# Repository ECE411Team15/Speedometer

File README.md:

# Speedometer
ECE 411, Fall 2017, Speedometer project.

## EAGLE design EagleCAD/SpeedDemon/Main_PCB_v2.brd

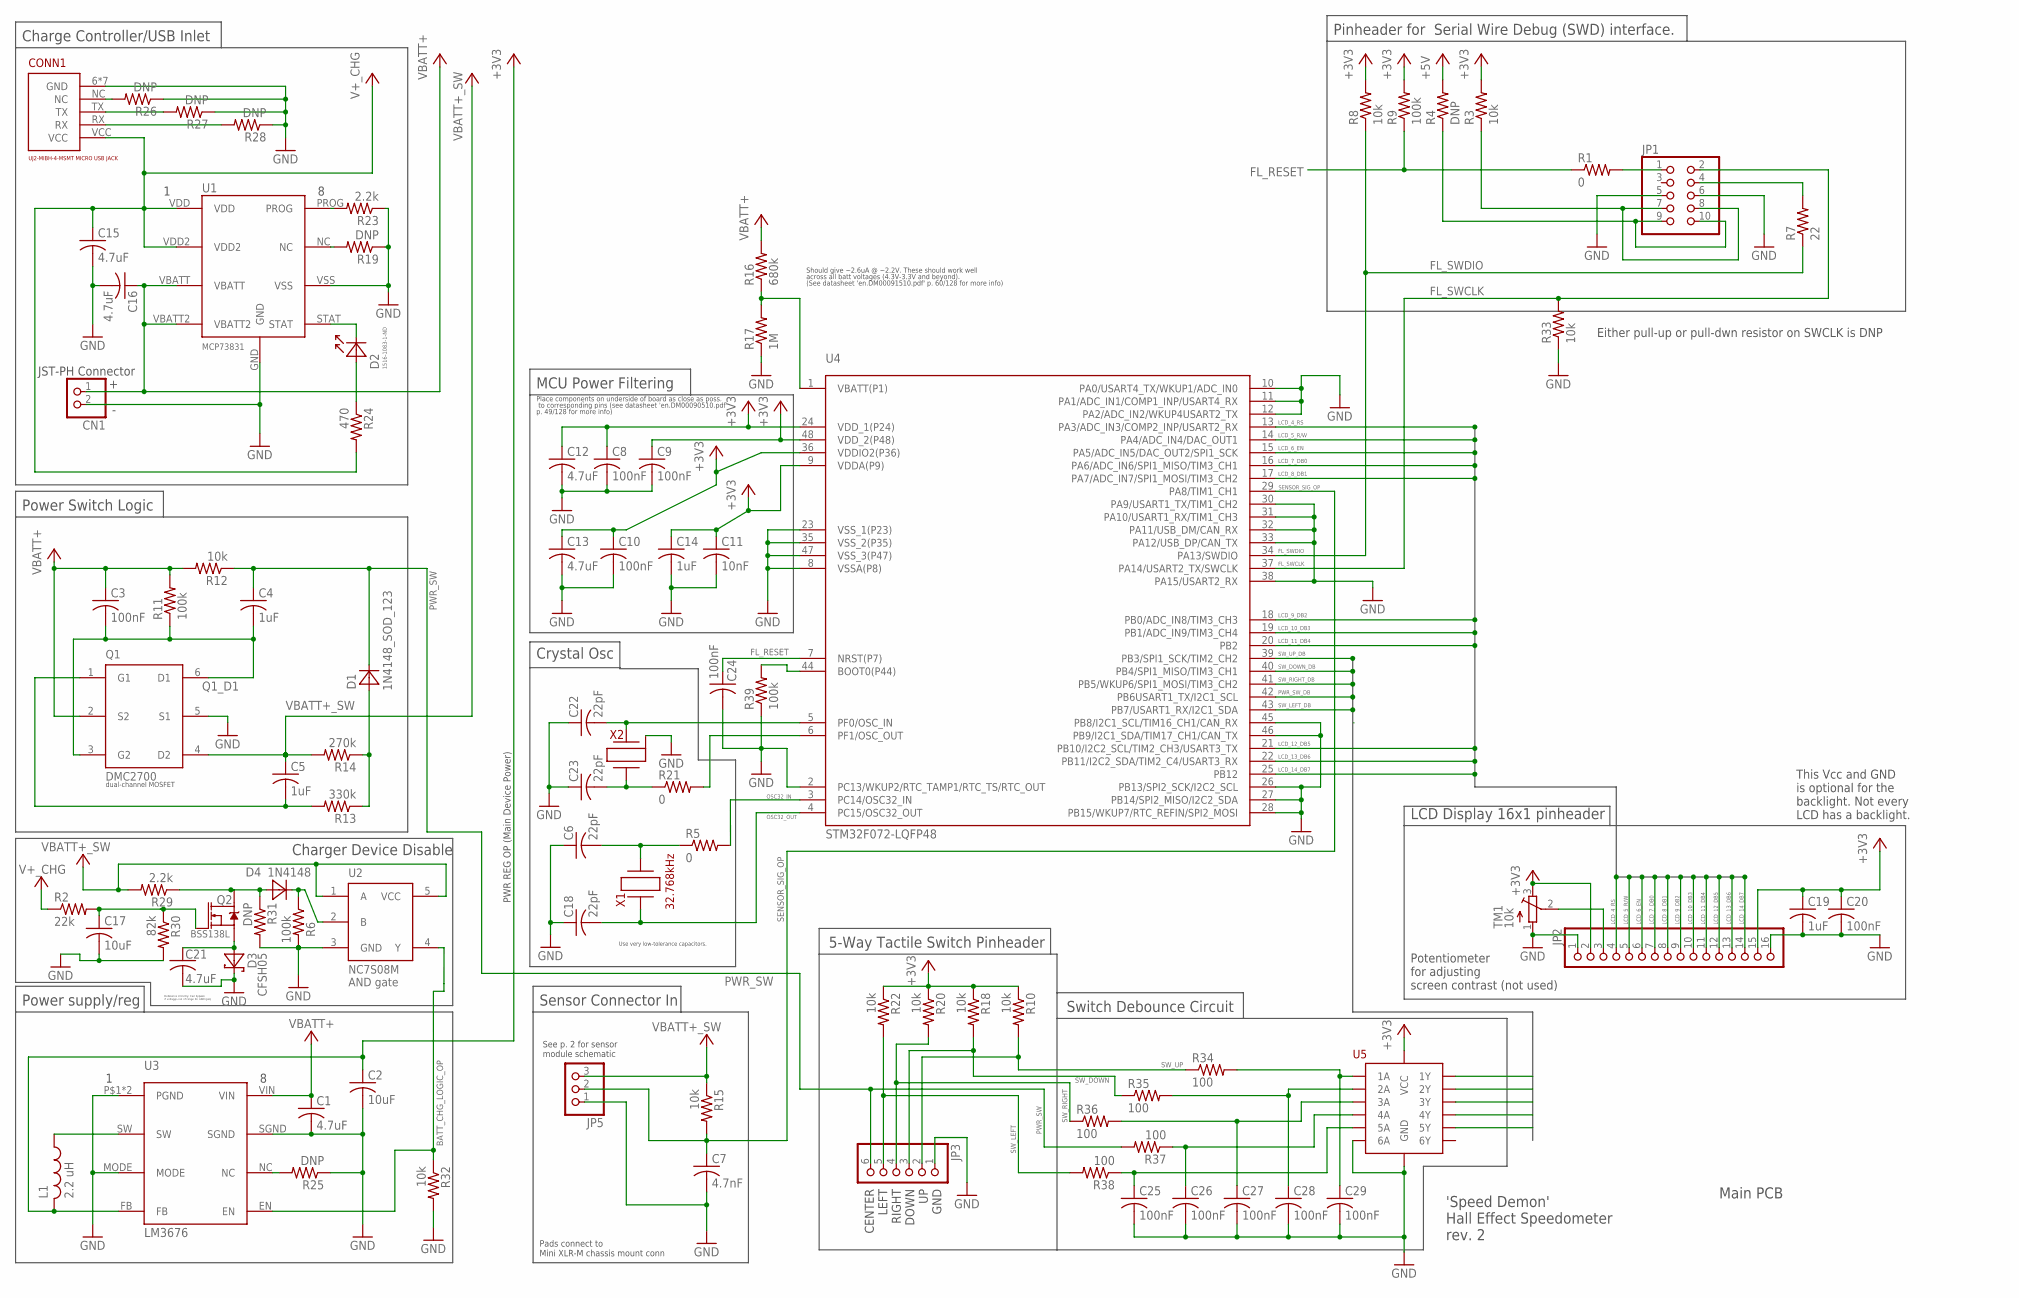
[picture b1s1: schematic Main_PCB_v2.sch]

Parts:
C1, C12, C13, C15, C16, C21: 4.7uF; C_0805
C2, C17: 10uF; C_0805
C3, C8, C9, C10, C20, C24, C25, C26, C27, C28, C29: 100nF; C_0805
C4, C5, C14, C19: 1uF; C_0805
C6, C18, C22, C23: 22pF; C_0805
C7: 4.7nF; C_0805
C11: 10nF; C_0805
CN1: JST_2PIN-SMT-RA; JST-PH-2-SMT-RA
CONN1: USB_JACK_102-4008-1-ND_USB-MICRO-B; USB_JACK_102-4008-1-ND_UJ2-MIBH-4-MSMT-TR
D1: 1N4148_SOD_123; D_SOD_123
D2: LED_0805
D3: CFSH05; SOD-882
D4: 1N4148; D_SOD_123
JP1: PINHD-2X5; 2X05
JP2: PINHD-1X16; 1X16
JP3: PINHD-1X6; 1X06
JP5: PINHD-1X3; 1X03
L1: 2.2 uH; NONSTANDARD_IND
Q1: DMC2700; SOT-23-6
Q2: BSS138L; TO-236
R1, R5: 0; R0805
R2: 22k; R_0805
R3, R8, R33: 10k; R0805
R4: DNP; R0805
R6, R11, R39: 100k; R_0805
R7: 22; R0805
R9: 100k; R0805
R10, R12, R15, R18, R20, R22, R32: 10k; R_0805
R13: 330k; R_0805
R14: 270k; R_0805
R16: 680k; R_0805
R17: 1M; R_0805
R19, R25, R26, R27, R28, R31: DNP; R_0805
R21: 0; R_0805
R23, R29: 2.2k; R_0805
R24: 470; R_0805
R30: 82k; R_0805
R34, R35, R36, R37, R38: 100; R_0805
TM1: 10k; TRIM-3386
U1: MCP73831_8-DFN; 8-DFN-(2X3)
U2: NC7S08M; SOT-23-5
U3: LM3676; WSON
U4: STM32F072-LQFP48; LQFP48
U5: SN74LV14A_HEX_SHMITT; S-PVFQN-N14
X1: 32.768kHz; CRYSTAL_OSC_3.2X1.5
X2: ABM3B-8.000MHZ-10-D-1-G-T; 4-SMD

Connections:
+3V3: C2.1, C8.1, C9.1, C10.1, C11.1, C12.1, C13.1, C14.1, C19.1, C20.1, JP2.2, JP2.15, L1.P$2 (2), R3.2, R8.2, R9.2, R10.1, R18.1, R20.1, R22.1, TM1.3 (E), U3.FB, U4.9 (VDDA(P9)), U4.24 (VDD_1(P24)), U4.36 (VDDIO2(P36)), U4.48 (VDD_2(P48)), U5.P$14 (VCC)
+5V: R4.2
+V+_CHG: C15.1, CONN1.VCC, R2.1, R24.2, U1.VDD, U1.VDD2
BATT_CHG_LOGIC_OP: R32.1, U2.4 (Y), U3.EN
FL_RESET: C24.1, R1.1, R9.1, U4.7 (NRST(P7))
FL_SWCLK: JP1.2, R33.2, U4.37 (PA14/USART2_TX/SWCLK)
FL_SWDIO: R7.1, R8.1, U4.34 (PA13/SWDIO)
GND: C1.2, C2.2, C6.1, C7.2, C8.2, C9.2, C10.2, C11.2, C12.2, C13.2, C14.2, C15.2, C16.2, C17.2, C18.1, C19.2, C20.2, C21.2, C22.1, C23.1, C24.2, C25.2, C26.2, C27.2, C28.2, C29.2, CN1.2 (1), CONN1.6 (GND), CONN1.7 (GND), CONN1.8 (GND), CONN1.9 (GND), CONN1.10 (GND), CONN1.11 (GND), CONN1.GND, D3.P$2 (C), JP1.5, JP1.6, JP2.1, JP2.16, JP3.1, JP5.1, Q1.5 (S1), R6.2, R17.1, R19.1, R23.1, R25.1, R26.1, R27.1, R28.1, R30.2, R31.2, R32.2, R33.1, R39.1, TM1.1 (A), U1.GND, U1.VSS, U2.3 (GND), U3.MODE, U3.P$1 (PGND), U3.PGND, U3.SGND, U4.2 (PC13/WKUP2/RTC_TAMP1/RTC_TS/RTC_OUT), U4.8 (VSSA(P8)), U4.10 (PA0/USART4_TX/WKUP1/ADC_IN0), U4.11 (PA1/ADC_IN1/COMP1_INP/USART4_RX), U4.12 (PA2/ADC_IN2/WKUP4USART2_TX), U4.23 (VSS_1(P23)), U4.26 (PB13/SPI2_SCK/I2C2_SCL), U4.27 (PB14/SPI2_MISO/I2C2_SDA), U4.28 (PB15/WKUP7/RTC_REFIN/SPI2_MOSI), U4.30 (PA9/USART1_TX/TIM1_CH2), U4.31 (PA10/USART1_RX/TIM1_CH3), U4.32 (PA11/USB_DM/CAN_RX), U4.33 (PA12/USB_DP/CAN_TX), U4.35 (VSS_2(P35)), U4.38 (PA15/USART2_RX), U4.45 (PB8/I2C1_SCL/TIM16_CH1/CAN_RX), U4.46 (PB9/I2C1_SDA/TIM17_CH1/CAN_TX), U4.47 (VSS_3(P47)), U5.GND, U5.P$7 (GND), U5.P$13 (6A), X2.P$02, X2.P$04
LCD_4_RS: JP2.4, U4.13 (PA3/ADC_IN3/COMP2_INP/USART2_RX)
LCD_5_R/W: JP2.5, U4.14 (PA4/ADC_IN4/DAC_OUT1)
LCD_6_EN: JP2.6, U4.15 (PA5/ADC_IN5/DAC_OUT2/SPI1_SCK)
LCD_7_DB0: JP2.7, U4.16 (PA6/ADC_IN6/SPI1_MISO/TIM3_CH1)
LCD_8_DB1: JP2.8, U4.17 (PA7/ADC_IN7/SPI1_MOSI/TIM3_CH2)
LCD_9_DB2: JP2.9, U4.18 (PB0/ADC_IN8/TIM3_CH3)
LCD_10_DB3: JP2.10, U4.19 (PB1/ADC_IN9/TIM3_CH4)
LCD_11_DB4: JP2.11, U4.20 (PB2)
LCD_12_DB5: JP2.12, U4.21 (PB10/I2C2_SCL/TIM2_CH3/USART3_TX)
LCD_13_DB6: JP2.13, U4.22 (PB11/I2C2_SDA/TIM2_C4/USART3_RX)
LCD_14_DB7: JP2.14, U4.25 (PB12)
unnamed: C5.2, Q1.1 (G1), R13.2
unnamed: JP1.1, R1.2
unnamed: JP1.9, JP1.10, R4.1
unnamed: R5.2, U4.3 (PC14/OSC32_IN)
unnamed: JP1.7, JP1.8, R3.1
unnamed: R16.1, R17.2, U4.1 (VBATT(P1))
unnamed: JP1.4, R7.2
unnamed: R39.2, U4.44 (BOOT0(P44))
unnamed: D4.2 (C), R6.1, U2.2 (B)
unnamed: L1.P$1 (1), U3.SW
unnamed: R21.2, U4.6 (PF1/OSC_OUT)
unnamed: JP2.3, TM1.2 (S)
unnamed: D1.1 (A), R13.1, R14.1
unnamed: C17.1, Q2.1 (G), R2.2, R30.1
unnamed: C22.2, U4.5 (PF0/OSC_IN), X2.P$01 (1)
unnamed: C23.2, R21.1, X2.P$03 (2)
unnamed: D4.1 (A), Q2.3 (D), R29.1, R31.1
unnamed: C21.1, D3.P$1 (A), Q2.2 (S)
unnamed: C25.1, R38.1, U5.P$11 (5A)
unnamed: C26.1, R37.1, U5.P$9 (4A)
unnamed: C27.1, R36.2, U5.P$5 (3A)
unnamed: C28.1, R35.2, U5.P$3 (2A)
unnamed: C29.1, R34.2, U5.P$1 (1A)
unnamed: D2.2 (C), U1.STAT
unnamed: R19.2, U1.NC
unnamed: D2.1 (A), R24.1
unnamed: R23.2, U1.PROG
unnamed: R25.2, U3.NC
unnamed: CONN1.NC, R26.2
unnamed: CONN1.TX, R27.2
unnamed: CONN1.RX, R28.2
OSC32_IN: C6.2, R5.1, X1.P$1 (1)
OSC32_OUT: C18.2, U4.4 (PC15/OSC32_OUT), X1.P$2 (2)
PWR_SW: C4.1, D1.2 (C), JP3.6, R12.1, R37.2
PWR_SW_DB: U4.42 (PB6USART1_TX/I2C1_SCL), U5.P$8 (4Y)
Q1_D1: C3.2, C4.2, Q1.3 (G2), Q1.6 (D1), R11.1
SENSOR_SIG_OP: C7.1, JP5.2, R15.2, U4.29 (PA8/TIM1_CH1)
SW_DOWN: JP3.3, R18.2, R35.1
SW_DOWN_DB: U4.40 (PB4/SPI1_MISO/TIM3_CH1), U5.P$4 (2Y)
SW_LEFT: JP3.5, R22.2, R38.2
SW_LEFT_DB: U4.43 (PB7/USART1_RX/I2C1_SDA), U5.P$10 (5Y)
SW_RIGHT: JP3.4, R20.2, R36.1
SW_RIGHT_DB: U4.41 (PB5/WKUP6/SPI1_MOSI/TIM3_CH2), U5.P$6 (3Y)
SW_UP: JP3.2, R10.2, R34.1
SW_UP_DB: U4.39 (PB3/SPI1_SCK/TIM2_CH2), U5.P$2 (1Y)
VBATT+: C1.1, C3.1, C16.1, CN1.1 (2), Q1.2 (S2), R11.2, R12.2, R16.2, U1.VBATT, U1.VBATT2, U3.VIN
VBATT+_SW: C5.1, JP5.3, Q1.4 (D2), R14.2, R15.1, R29.2, U2.1 (A), U2.5 (VCC)

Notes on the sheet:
Pinheader for Serial Wire Debug (SWD) interface.
Power supply/reg
Power Switch Logic
Place components on underside of board as close as poss.
to corresponding pins (see datasheet 'en.DM00090510.pdf'
p. 49/128 for more info)
MCU Power Filtering
Should give ~2.6uA @ ~2.2V. These should work well
across all batt voltages (4.3V-3.3V and beyond).
(See datasheet 'en.DM00091510.pdf' p. 60/128 for more info)
This Vcc and GND is optional for the backlight. Not every LCD has a backlight.
Potentiometer for adjusting screen contrast (not used)
LCD Display 16x1 pinheader
5-Way Tactile Switch Pinheader
dual-channel MOSFET
Charge Controller/USB Inlet
Charger Device Disable
PWR REG OP (Main Device Power)
Sensor Connector In
Pads connect to Mini XLR-M chassis mount conn
'Speed Demon' Hall Effect Speedometer rev. 2
Main PCB
See p. 2 for sensor module schematic
Crystal Osc
CENTER LEFT RIGHT DOWN UP GND
Use very low-tolerance capacitors.
JST-PH Connector
Debounce circuitry. Can bypass if voltages out of range for AND gate.
Either pull-up or pull-dwn resistor on SWCLK is DNP
Switch Debounce Circuit

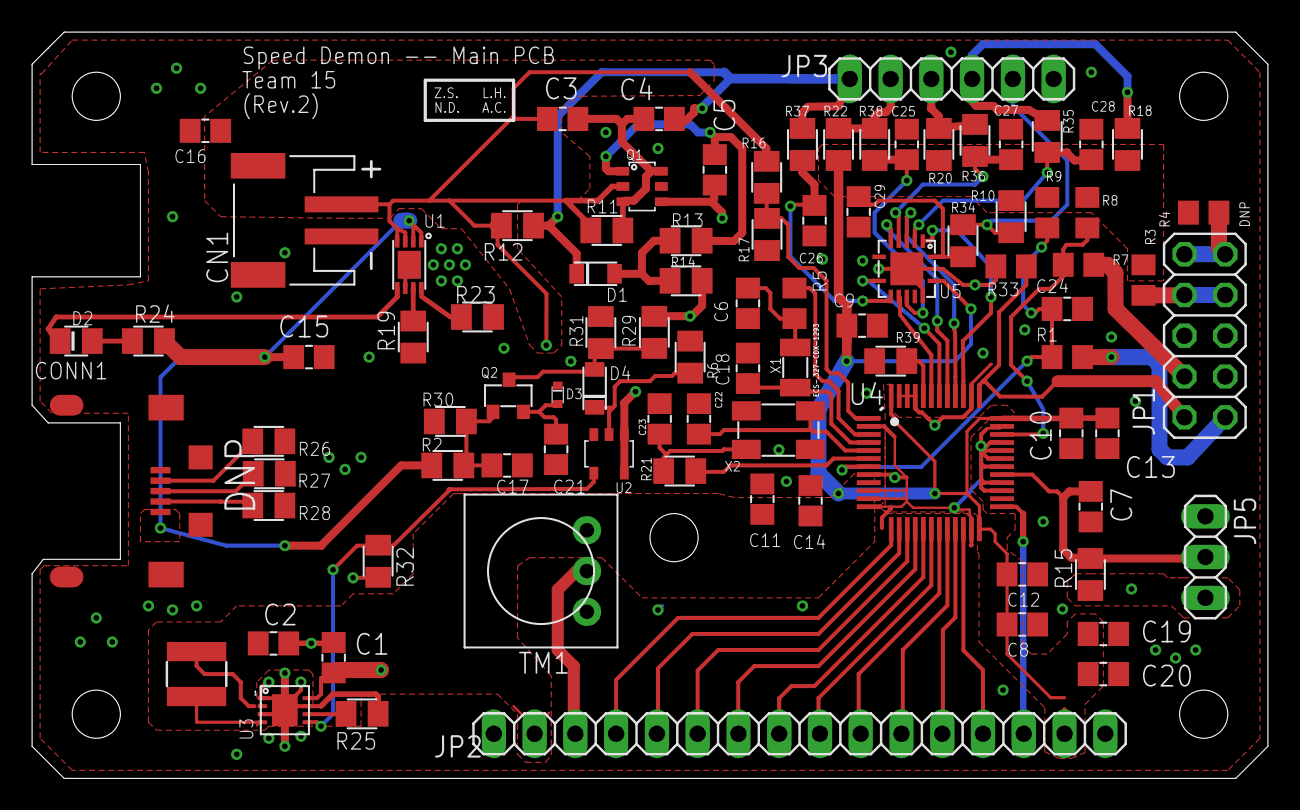
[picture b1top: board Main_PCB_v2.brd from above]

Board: 2 copper layers, 77.0 x 46.5 mm, 89 parts (0 on the bottom side), 65 nets.

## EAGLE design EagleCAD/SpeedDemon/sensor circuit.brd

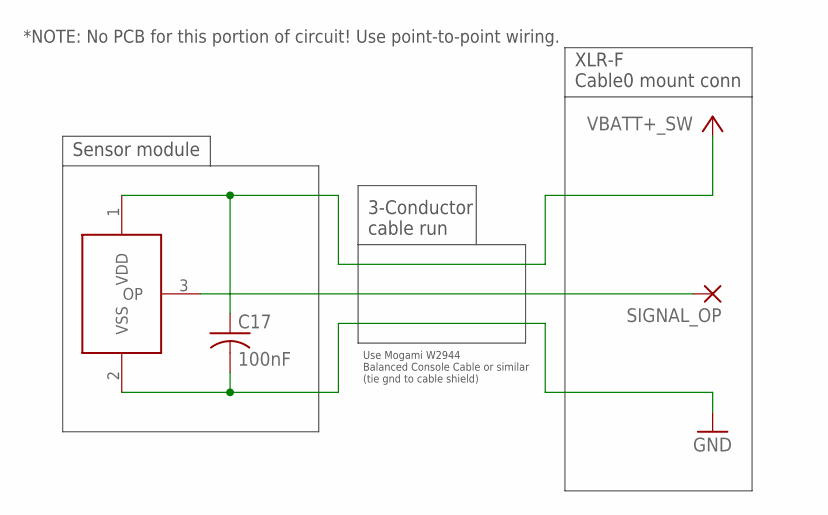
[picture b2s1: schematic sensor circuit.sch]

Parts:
C17: 100nF; C025-024X044
SIGNAL_OP: 1,6/0,8
U1A: US5881; TO-92

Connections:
GND: C17.2, U1A.2 (VSS)
unnamed: SIGNAL_OP.1, U1A.3 (OP)
VBATT+_SW: C17.1, U1A.1 (VDD)

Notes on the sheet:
Sensor module
XLR-F Cable0 mount conn
3-Conductor cable run
Use Mogami W2944 Balanced Console Cable or similar (tie gnd to cable shield)
*NOTE: No PCB for this portion of circuit! Use point-to-point wiring.

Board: 2 copper layers, 3 parts (0 on the bottom side), 3 nets, no tracks yet.

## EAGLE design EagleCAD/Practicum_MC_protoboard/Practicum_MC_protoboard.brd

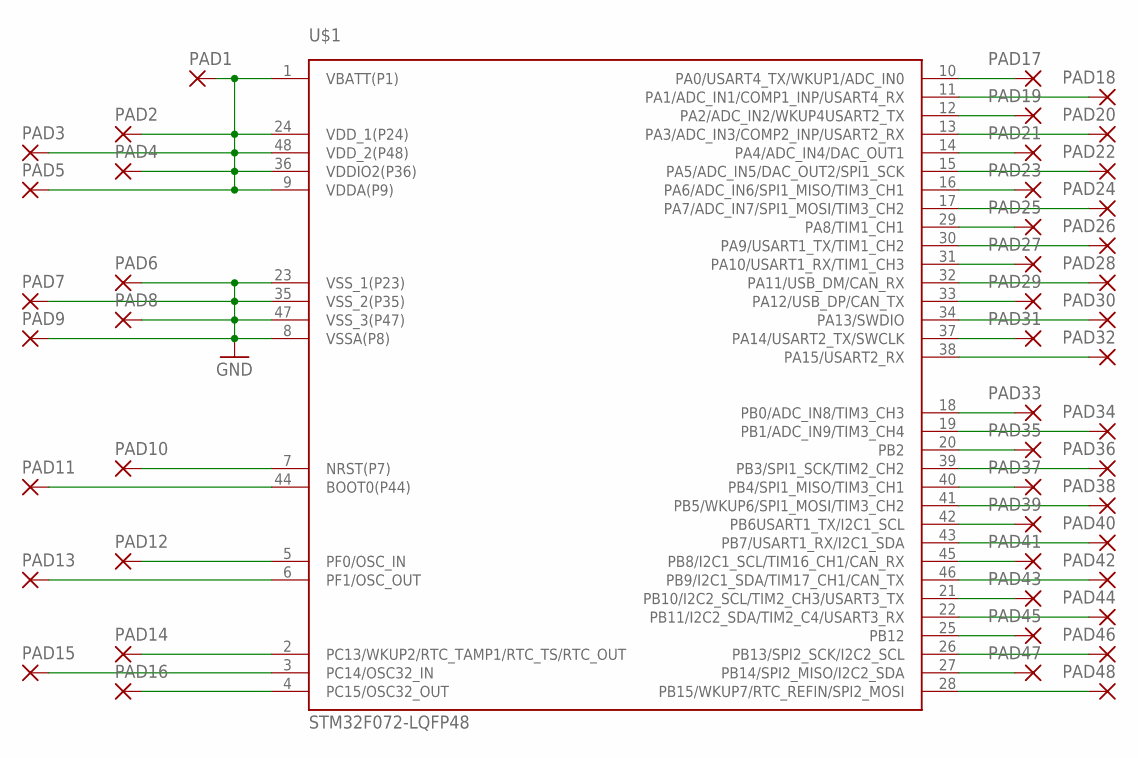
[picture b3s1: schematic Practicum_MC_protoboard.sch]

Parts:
PAD1, PAD2, PAD3, PAD4, PAD5, PAD6, PAD7, PAD8, PAD9, PAD10, PAD11, PAD12, PAD13, PAD14, PAD15, PAD16, PAD17, PAD18, PAD19, PAD20, PAD21, PAD22, PAD23, PAD24, PAD25, PAD26, PAD27, PAD28, PAD29, PAD30, PAD31, PAD32, PAD33, PAD34, PAD35, PAD36, PAD37, PAD38, PAD39, PAD40, PAD41, PAD42, PAD43, PAD44, PAD45, PAD46, PAD47, PAD48: SMD5; SMD2,54-5,08
U$1: STM32F072-LQFP48; LQFP48

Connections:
GND: PAD6.1, PAD7.1, PAD8.1, PAD9.1, U$1.8 (VSSA(P8)), U$1.23 (VSS_1(P23)), U$1.35 (VSS_2(P35)), U$1.47 (VSS_3(P47))
unnamed: PAD33.1, U$1.18 (PB0/ADC_IN8/TIM3_CH3)
unnamed: PAD34.1, U$1.19 (PB1/ADC_IN9/TIM3_CH4)
unnamed: PAD35.1, U$1.20 (PB2)
unnamed: PAD36.1, U$1.39 (PB3/SPI1_SCK/TIM2_CH2)
unnamed: PAD37.1, U$1.40 (PB4/SPI1_MISO/TIM3_CH1)
unnamed: PAD38.1, U$1.41 (PB5/WKUP6/SPI1_MOSI/TIM3_CH2)
unnamed: PAD39.1, U$1.42 (PB6USART1_TX/I2C1_SCL)
unnamed: PAD40.1, U$1.43 (PB7/USART1_RX/I2C1_SDA)
unnamed: PAD41.1, U$1.45 (PB8/I2C1_SCL/TIM16_CH1/CAN_RX)
unnamed: PAD42.1, U$1.46 (PB9/I2C1_SDA/TIM17_CH1/CAN_TX)
unnamed: PAD43.1, U$1.21 (PB10/I2C2_SCL/TIM2_CH3/USART3_TX)
unnamed: PAD44.1, U$1.22 (PB11/I2C2_SDA/TIM2_C4/USART3_RX)
unnamed: PAD45.1, U$1.25 (PB12)
unnamed: PAD46.1, U$1.26 (PB13/SPI2_SCK/I2C2_SCL)
unnamed: PAD47.1, U$1.27 (PB14/SPI2_MISO/I2C2_SDA)
unnamed: PAD48.1, U$1.28 (PB15/WKUP7/RTC_REFIN/SPI2_MOSI)
unnamed: PAD32.1, U$1.38 (PA15/USART2_RX)
unnamed: PAD31.1, U$1.37 (PA14/USART2_TX/SWCLK)
unnamed: PAD30.1, U$1.34 (PA13/SWDIO)
unnamed: PAD29.1, U$1.33 (PA12/USB_DP/CAN_TX)
unnamed: PAD28.1, U$1.32 (PA11/USB_DM/CAN_RX)
unnamed: PAD27.1, U$1.31 (PA10/USART1_RX/TIM1_CH3)
unnamed: PAD26.1, U$1.30 (PA9/USART1_TX/TIM1_CH2)
unnamed: PAD25.1, U$1.29 (PA8/TIM1_CH1)
unnamed: PAD24.1, U$1.17 (PA7/ADC_IN7/SPI1_MOSI/TIM3_CH2)
unnamed: PAD23.1, U$1.16 (PA6/ADC_IN6/SPI1_MISO/TIM3_CH1)
unnamed: PAD22.1, U$1.15 (PA5/ADC_IN5/DAC_OUT2/SPI1_SCK)
unnamed: PAD21.1, U$1.14 (PA4/ADC_IN4/DAC_OUT1)
unnamed: PAD20.1, U$1.13 (PA3/ADC_IN3/COMP2_INP/USART2_RX)
unnamed: PAD19.1, U$1.12 (PA2/ADC_IN2/WKUP4USART2_TX)
unnamed: PAD18.1, U$1.11 (PA1/ADC_IN1/COMP1_INP/USART4_RX)
unnamed: PAD17.1, U$1.10 (PA0/USART4_TX/WKUP1/ADC_IN0)
unnamed: PAD1.1, PAD2.1, PAD3.1, PAD4.1, PAD5.1, U$1.1 (VBATT(P1)), U$1.9 (VDDA(P9)), U$1.24 (VDD_1(P24)), U$1.36 (VDDIO2(P36)), U$1.48 (VDD_2(P48))
unnamed: PAD10.1, U$1.7 (NRST(P7))
unnamed: PAD11.1, U$1.44 (BOOT0(P44))
unnamed: PAD12.1, U$1.5 (PF0/OSC_IN)
unnamed: PAD13.1, U$1.6 (PF1/OSC_OUT)
unnamed: PAD14.1, U$1.2 (PC13/WKUP2/RTC_TAMP1/RTC_TS/RTC_OUT)
unnamed: PAD15.1, U$1.3 (PC14/OSC32_IN)
unnamed: PAD16.1, U$1.4 (PC15/OSC32_OUT)

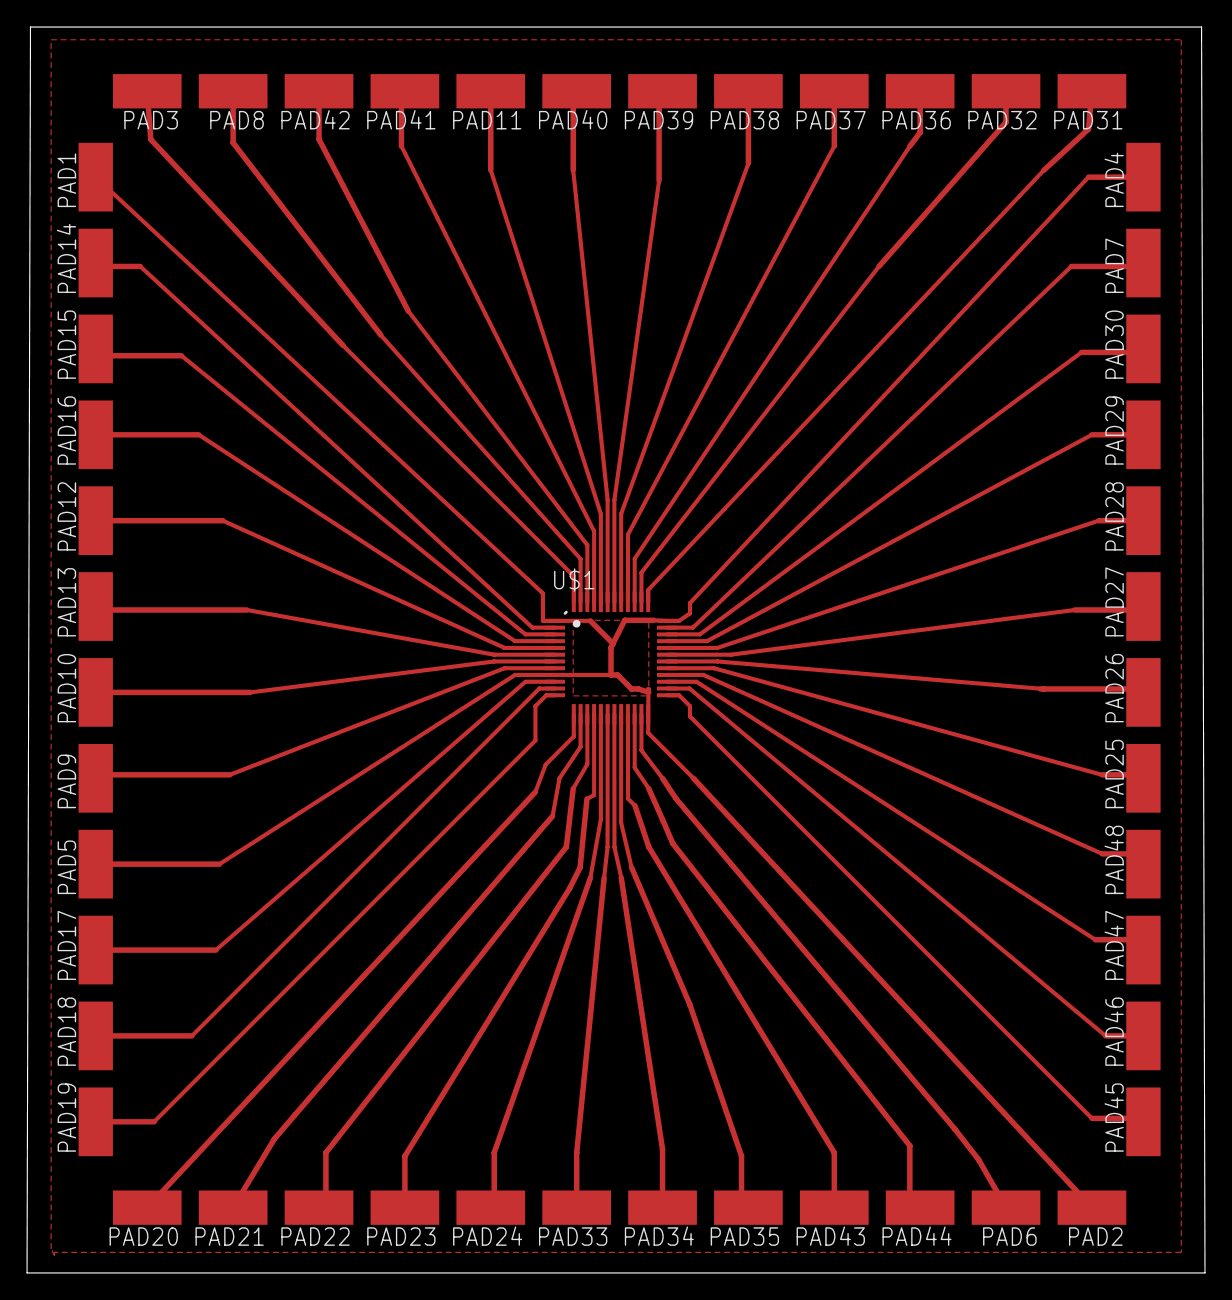
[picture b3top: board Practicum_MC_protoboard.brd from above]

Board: 2 copper layers, 87.1 x 92.1 mm, 49 parts (0 on the bottom side), 41 nets.

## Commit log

2017-10-07 Adding Helpful Manuals
    the developers webinar is great for a high level overview.
2017-10-10 Adding my Data Log
    This log is for the work Andrew Capatina will be performing. The log keeps track of basic information needed for our project.
2017-10-10 Initial Hall Sensor Reading
    Graph of voltage output for hall effect sensor.
2017-10-12 reorganized root folder with subfolders to prevent clutter.
2017-10-12 Added WPR blank folder and naming convention
2017-10-12 Add files via upload
    The specific package I ordered is A3212EUA-T
2017-10-12 added EagleCAD files for MCU dev board
2017-10-12 added CNC mill files for dev board
2017-10-12 Add files via upload
    Week 3
2017-10-12 more re-org
2017-10-13 modified dev board layout slightly
2017-10-14 Create wk03_capatina_WPR
2017-10-14 Create folder_info
2017-10-14 Create datasheet_links
2017-10-14 Create wk03_linyi_report
2017-10-14 Rename wk03_linyi_report to wk03_linyi_WPR
2017-10-14 final version of MCU dev board
2017-10-14 Sensor Data
    Latest test run with U58 sensor
2017-10-14 Sensor Data
    Latest test data from U58
2017-10-14 edited WPR
2017-10-15 Updated BOM
2017-10-15 Updated wk3 WPR
2017-10-17 Update wk03_capatina_WPR
2017-10-17 Test
2017-10-18 Added revised project requirements doc
2017-10-18 Update wk03_linyi_WPR
2017-10-18 Rename wk03_linyi_WPR to wk03_Linyi_WPR
2017-10-18 Added wording and clarification.
2017-10-19 slight mod to requirements doc
2017-10-19 Week 4 WPR
    ¯\_(ツ)_/¯
2017-10-20 First version of eaglecad schematic
2017-10-20 Changed folder name from "schematic" to "EagleCAD" because we are storing the entire Eagle project here.
2017-10-21 small schem update
2017-10-21 datasheet reorg
2017-10-21 schematic changes
2017-10-21 Here's my report.
2017-10-21 Zach and I started the EagleCAD schematic.
2017-10-21 This is the switching voltage regulator I made.
2017-10-21 Zach I modified the schematic and added the Serial Wire Debug (SWD) connections based off Linyi's document. Let me know what you think. We should double check this together.
2017-10-21 Zach checkout the schematic. I added the SWD connections. We should review this together.
2017-10-21 added partial power circuit to schematic, added 0805_generics.lbr (generic 0805 SMD RCL parts) to EagleCAD folder
2017-10-21 added work-in-progress circuit sim for on button timing
2017-10-22 Added LTSpice sim of working power switching control circuit
2017-10-22 added datasheet for DMC2700UDM.pdf (dual-channel MOS package) for power-on circuit
2017-10-22 Create Required Pins
2017-10-22 Added power switch logic to schematic (mostly done). Added related parts to new library.
2017-10-22 no message
2017-10-22 Added 1n4148 SMD package to library and to power button schematic
2017-10-23 More added to schem, incl. power scheme for MCU and seonsor input section. NOTE: Working SMD passives library has been renamed LCRD_SMD_generics.lbr
2017-10-23 Create READ_ME
2017-10-23 MCU pinout
    Pinout needed for schematic
2017-10-23 Made revision
    Included pins for IO power and ground.
2017-10-23 Update Requirements
    To include VDDA and VSSA
2017-10-23 Added WPR, tested dual output for mode/pwr switch (it works as SPST if it's properly buffered!)
2017-10-23 lab test data of power on circuit added (it works)
2017-10-23 edit switch lab results
2017-10-23 Added thermal pad to switching regulator library part. Updated schematic.
2017-10-24 Update wk04_capatina_WPR
2017-10-24 added results of test build for charger power interrupt
2017-10-24 updated LTSpice power control schematic to include charger interrupt (not pictured: AND gate on output).
2017-10-25 Added LCD and 5-way button to schematic.
2017-10-25 5-way tactile switch library.
2017-10-25 Mechanical drawings.
2017-10-25 removed some dumb autosaves
2017-10-25 Power section of schematic finished. Some parts added to libraries.
2017-10-25 Schematic update, passed ERC. Added second page with sensor module. Added several parts libraries.
2017-10-25 tiny edits
2017-10-25 Fixed frame of second page
2017-10-26 Copy of schematic for class assignment.
2017-10-26 added direct link to schematic on front page
2017-10-26 Deleted
2017-10-29 Week 5 Report
2017-10-29 Update wk05_capatina_WPR
2017-10-30 added 'WPRs/wk05_Stamler_WPR.txt'
2017-10-30 GIT issue double-commit
2017-10-30 added WPRs/wk05_Stamler_WPR.txt
2017-10-30 My WPR for week 5
2017-10-31 added datasheets for LCD screen
2017-10-31 Updated project plan
2017-10-31 added external OSC circuit to schematic, several datasheets
2017-11-01 Updated the 5-way button
2017-11-01 Updated 5-way tactile switch
2017-11-01 Schematic updates, labeling, bus bars. ERC passed. Nathan will finalize tonight.
2017-11-02 Updated battery connector.
2017-11-02 Added in some parts that we'll need to order soon.
2017-11-02 ECE411 Project Schedule 11/1
    Project schedule uploaded on November 1st.
2017-11-03 The breakout board for the 5-way tactile switch is complete. Check it out.
2017-11-03 Started a board layout
2017-11-03 Modded switch breakout board, sent design away. Also added OSHPark design rules file
2017-11-03 cleanup
2017-11-03 Reviewed
2017-11-04 Added 5-way tactile switch order.
2017-11-04 board layout.. needs some work
2017-11-04 Draft layout. Moved power reg circuit as far away from everything else as possible to minimize possible noise issues. Also poured polygons for power planes
2017-11-05 fixed inductor choice, picked one that meets spec for the pwr converter
2017-11-05 Zach I added stitching vias to stitch the top and bottom gnd planes together. I also made the board smaller by pulling the top down and shifting components.
2017-11-05 Here is my week 6 report
2017-11-05 Fixed drill hole
2017-11-05 Fixed drill holes
2017-11-05 Incorporated Nathan's v.2 revs and also did some more power planing
2017-11-05 Fixed several DRC errors
2017-11-06 Adding Low Level Algorithm
    Added low level algorithm for speed conversion.
2017-11-06 Andrew Capatina WPR
    Week 6
2017-11-06 added WPR
2017-11-06 BOM additions
2017-11-06 board revisions, potential switch cap datasheet
2017-11-07 Here is what we have so far.
2017-11-07 added basic mechanical drawings (no Z dimension) to allow beginning case design
2017-11-07 Moved some blocks onto page 4.
2017-11-08 Added level 1 power supply.
2017-11-09 HW5 added
2017-11-09 hw5 update
2017-11-09 Completed version
2017-11-09 layout link added
2017-11-09 Organized LCD datasheets
2017-11-12 updated schematic/layout with pwr inlet debounce circuit and added center switch connectivity to MCU. Other small organizational changes.
2017-11-12 Changed layout to maximize distance between power inductor and everything else
2017-11-12 several small changes to layout to improve ground planing
2017-11-12 Added WPRs, finished changes for debounce circuit.
2017-11-12 Rename wk06_capatina_WPR to wk07_capatina_WPR
2017-11-13 Week 7
2017-11-13 Version 1.3
    Latest MCU pinout.
2017-11-13 minor library/board tweaks
2017-11-13 added 8MHz oscillator citcuit to layout and schematic
2017-11-13 schematic/layout detail work.
2017-11-13 final changes to power defeat logic
2017-11-14 Prototype software
    For interfacing with LCD and hall effect sensor.
2017-11-14 Updated name of reference doc
    file cleanup
2017-11-15 Version 1.2 of prototype
    Added comments to code.
2017-11-15 final layout adjustments
2017-11-16 final board
2017-11-16 Ordered 4 Li-po batteries and 5 right-angle JST-PH connectors.
2017-11-16 Final Board/schem. Includes added debounce circuit for 5-way switch.
2017-11-16 tiny revision to final. SUBMITTED THIS VERSION TO FAB.
2017-11-17 Merge branch 'master' of https://github.com/ECE411Team15/Speedometer
    # Conflicts:
    # Bill of Material.xlsx
2017-11-18 Added files for OSH stencil. Updated BOM, including total cost per team member.
2017-11-20 Create wk08_capatina_WPR
2017-11-21 ZSS WPR wk8
2017-11-21 moved case mechanical drawings to new root-level folder
2017-11-22 Here is what Zach and I have for homework 7
2017-11-22 prototyping images
2017-11-22 Week 8 report
2017-11-26 added quick sample graphic
2017-11-27 Input Capture SW 2.0
    Latest and greatest of speed conversion algorithm. Comments were deleted because the comments were not added in the user section part of the code. The comments I'm referring to is the name and links 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
2017-11-27 Input Capture High Level 2.0
    Latest high level algorithm for input capture.
2017-11-27 Input Capture Low Level 2.0
    Added newest input capture low level algorithm.
2017-11-27 Create wk09_capatina_WPR
2017-11-27 added wk9 WPR
2017-11-27 For week 9
2017-11-30 SW Test Plan
    Software Test Plan
2017-11-30 Updated Software Test Diagram
    2.0 is newest as of 11/29/17
2017-11-30 Homework 7
2017-11-30 I modified the must-should-bonus requirements quite heavily. Check them out. I wanted the goals to be more realistic to what we will achieve.
2017-11-30 added updated schematic/layout to reflect board hacks
2017-12-02 Week 10... So much work this week >_<
2017-12-04 Updated some of my orders
2017-12-05 wk10 WPR added
2017-12-05 speedDemon Code!
    First version of code that is ready for the demo.
2017-12-05 Create wk10_capatina_WPR
    sorry i'm a bit late >_<
2017-12-05 Presentation
2017-12-05 BOM is almost complete. There are some things that need to be reviewed.
2017-12-06 Fixed the calculation for the cost of a single board.
2017-12-06 Presentation Update 2
    Updated Presentation, take a look
2017-12-06 BOM adjustments
2017-12-06 Made some changes to order of presentations
2017-12-06 Changed order of presenters
2017-12-06 Added Test Software
    This should be the remainder of the test software.
2017-12-06 Changed some wording
2017-12-06 READ DESCRIPTION
    speedDemon 2.0 is the version likely to be demoed.
    speedDemon 2.0.1 contains SAME functionality however is structured differently.
    - The goal of restructuring the code was to abstract all functionality from main, now we only have two functions being called in main.c.
    - Fixing a communication error when integrating the code.
2017-12-06 Added some more photos to the log folder
2017-12-06 Reordered some wording.
2018-01-09 I summed the total costs of what we each spent on the project.
2018-01-10 I added in the price of one more MCU that Andrew had purchased.
